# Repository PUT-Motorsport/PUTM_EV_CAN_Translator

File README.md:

# PUT Motorsport - CAN Translator
The module is responsible for communication between the motor inverter and the main bus. The translator transmits the speed set signals from the measurement card and logs the parameters from the inverter. All communication takes place over the CAN bus.

## Authors
* Piotr Kwiatkowski
* Bartosz Ptak

## Device
We used our own PCB, which was equipped with 2 CAN transmitters and a STM32F105RB microcontroller.

## Table of contents

- [Hardware setup](#Hardware-setup)
  * [Pinouts](#Pinouts)
  * [Clocks](#Clocks)
  * [Timers](#Timers)
  * [CANs](#CANs)
- [Software](#Software)
  * [CAN inverter functions](#CAN-inverter-functions)

## Hardware setup

### Pinouts

Active pinouts:

* CAN1_TX (`PA12`), CAN1_RX (`PA11`)
* CAN2_TX (`PB13`), CAN2_RX (`PB12`)
* RCC clock
* GPIO_LED_[1-6] for debugging

### Clocks

We used an external clock speed and set its frequency to **64 MHz** for (`HCLK`). This setting allowed to set the clock frequency of the peripherals to **32 MHz** (`PCLK1`).

### Timers

* `TIM2`:
    - **usage**: safety counting, 1 ms
    - **prescaler:** 999
    - **counter Period:** 63
    - **counter mode:** Up
    - **auto-reload:** Enable
* `TIM3`:
    - **usage**: send parameters to telemetry, 20 ms
    - **prescaler:** 19999
    - **counter Period:** 63
    - **counter mode:** Up
    - **auto-reload:** Enable

### CANs

* `CAN1`:
    - **usage**: main bus, measurement card, 500 kbps
    - **prescaler:** 4
    - **time quanta 1:** 13
    - **time quanta 2:** 2
    - **time quantum:** 125.0 ns

* `CAN2`:
    - **usage**: inverter bus, 500 kbps
    - **prescaler:** 4
    - **time quanta 1:** 13
    - **time quanta 2:** 2
    - **time quantum:** 125.0 ns

## Software

### CAN inverter functions

* `CAN_disable_controller_command` - inverter safety shutdown
* `CAN_set_speed_command` - set the APPS speed value in the range 0-500 (0-100%)
* `CAN_stop_speed_command` - set the speed value to 0
* `CAN_request_speed_command` - request that the inverter send information about the current speed
* `CAN_request_power_command` - request for the inverter to send information about the current current
* `CAN_request_igbt_temp_command` - request for the inverter to send information about the current igbt temperature
* `CAN_request_motor_temp_command` - request for the inverter to send information about the current motor temperature

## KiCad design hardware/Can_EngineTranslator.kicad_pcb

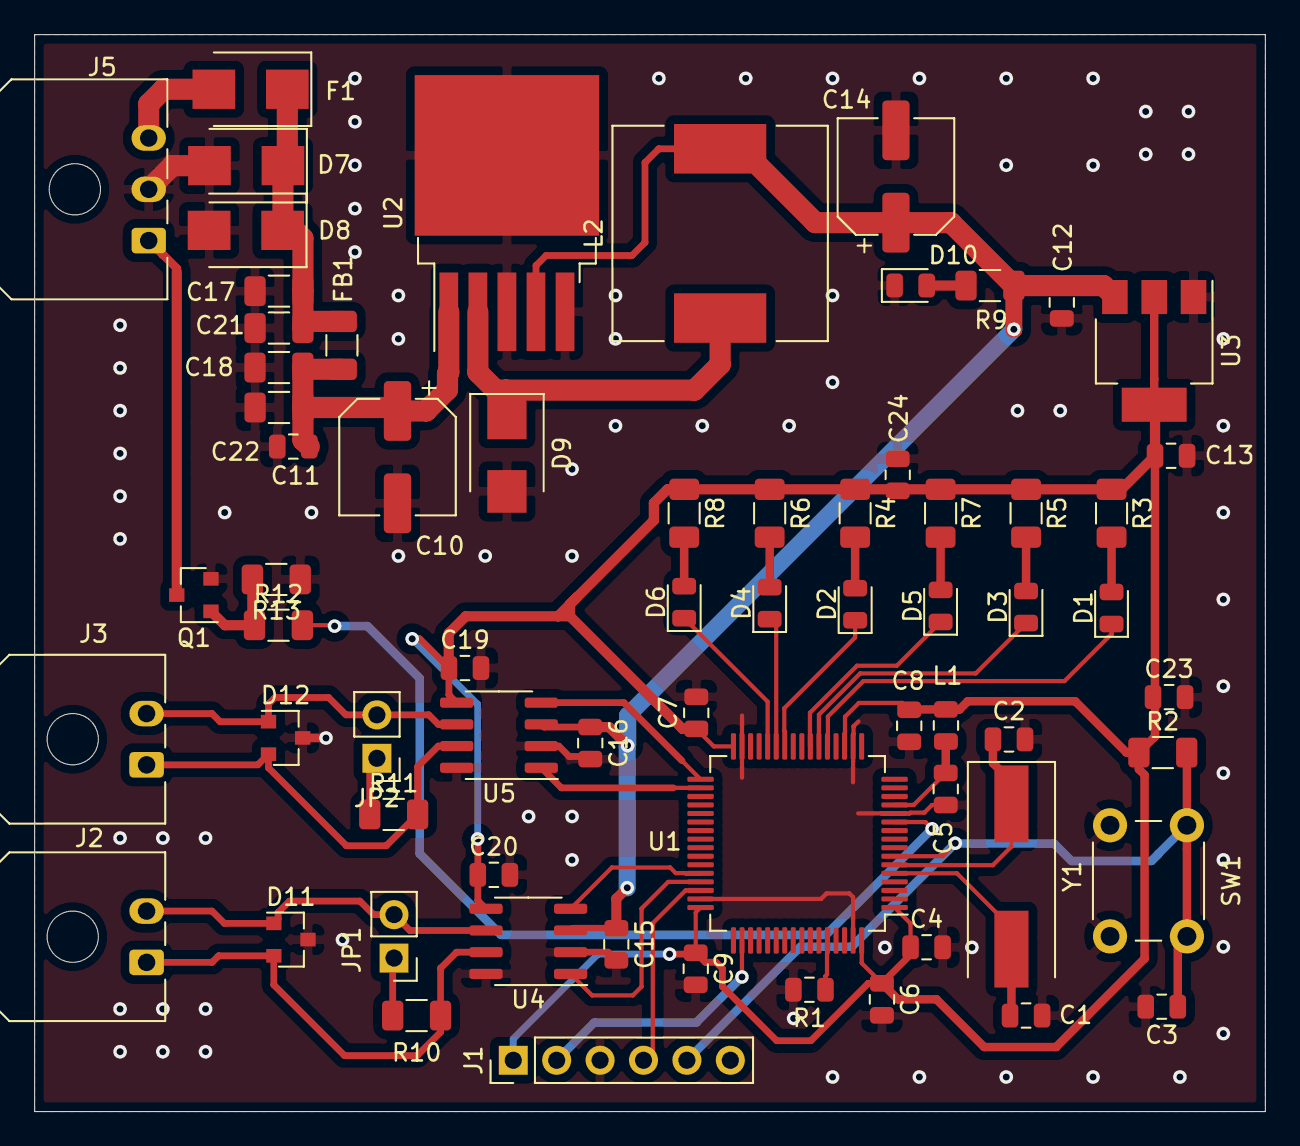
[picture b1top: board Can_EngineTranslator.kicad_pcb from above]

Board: 2 copper layers, 72.0 x 63.0 mm, 67 parts (0 on the bottom side), 40 nets.

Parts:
C1, C2: 22pF; C_0805_2012Metric
C3, C4, C5, C6, C7, C8, C9, C11, C12, C13, C15, C16, C19, C20, C23, C24: 100nF; C_0805_2012Metric
C10: 680uF; CP_Elec_6.3x7.7
C14: 220u; CP_Elec_6.3x7.7
C17, C18, C21, C22: CP_Small; C_1206_3216Metric
D1, D2, D3, D4, D5, D6, D10: LED; LED_0805_2012Metric
D7: 1SMA5937BT3G; D_SMB
D8, D9: SS24T3G; D_SMB
D11, D12: PESD2CAN.215; SOT-23
F1: Polyfuse; D_SMB
FB1: Ferrite_Bead_Small; R_1206_3216Metric
J1: ProgramerConnector; PinHeader_1x06_P2.54mm_Vertical
J2: CANcarConnector; Molex_Micro-Fit_3.0_43650-0200_1x02_P3.00mm_Horizontal
J3: CANinverterConnector; Molex_Micro-Fit_3.0_43650-0200_1x02_P3.00mm_Horizontal
J5: PowerOutputConnector; Molex_Micro-Fit_3.0_43650-0300_1x03_P3.00mm_Horizontal
JP1, JP2: Jumper; PinHeader_1x02_P2.54mm_Vertical
L1: L; L_0805_2012Metric
L2: 33u; L_12x12mm_H8mm
Q1: BSS138; SOT-23
R1: 100k; R_0805_2012Metric
R2, R13: 10k; R_1206_3216Metric
R3, R4, R5, R6, R7, R8, R9: 180; R_1206_3216Metric
R10, R11: 120R; R_1206_3216Metric
R12: 100; R_1206_3216Metric
SW1: SW_Push; SW_PUSH_6mm
U1: STM32F105RBTx; LQFP-64_10x10mm_P0.5mm
U2: LM2596S-5; TO-263-5_TabPin3
U3: LM1117-3.3; SOT-223-3_TabPin2
U4, U5: MCP2562-H-SN; SOIC-8_3.9x4.9mm_P1.27mm
Y1: Crystal 8 MHz; Crystal_SMD_HC49-SD

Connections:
+5V: C12.1, C14.1, C15.1, C16.1, L2.2, R9.1, U2.4, U3.3, U4.3, U5.3
CANcar_H: D11.2, J2.1, R10.2, U4.7
CANcar_L: D11.1, J2.2, JP1.2, U4.6
CANcar_RX: U1.44, U4.4
CANcar_TX: U1.45, U4.1
CANinverter_H: D12.2, J3.1, R11.2, U5.7
CANinverter_L: D12.1, J3.2, JP2.2, U5.6
CANinverter_RX: U1.33, U5.4
CANinverter_TX: U1.34, U5.1
NRST: C3.1, J1.5, R2.2, SW1.2, U1.7
unnamed: C1.1, U1.5, Y1.2
unnamed: C2.1, U1.6, Y1.1
unnamed: C5.1, L1.2, U1.13
unnamed: C10.1, C11.1, C18.1, C22.1, FB1.2, U2.1
unnamed: C17.1, C21.1, D7.1, D8.1, F1.1, FB1.1
unnamed: D1.1, U1.21
unnamed: D1.2, R3.2
unnamed: D2.1, U1.26
unnamed: D2.2, R4.2
unnamed: D3.1, U1.22
unnamed: D3.2, R5.2
unnamed: D4.1, U1.27
unnamed: D4.2, R6.2
unnamed: D5.1, U1.23
unnamed: D5.2, R7.2
unnamed: D6.1, U1.28
unnamed: D6.2, R8.2
unnamed: D9.1, L2.1, U2.2
unnamed: D10.2, R9.2
unnamed: JP1.1, R10.1
unnamed: JP2.1, R11.1
unnamed: Q1.1, R12.1, R13.2
unnamed: R1.1, U1.60
SWCLK: J1.2, U1.50
SWDIO: J1.4, U1.46
SW_GND: C1.2, C2.2, C3.2, C4.2, C5.2, C6.2, C7.2, C8.2, C9.2, C10.2, C11.2, C12.2, C13.2, C14.2, C15.2, C16.2, C17.2, C18.2, C19.2, C20.2, C21.2, C22.2, C23.2, C24.2, D7.2, D8.2, D9.2, D10.1, D11.3, D12.3, J1.3, J5.2, Q1.2, R1.2, R13.1, SW1.1, U1.12, U1.18, U1.31, U1.47, U1.63, U2.3, U2.5, U3.1, U4.2, U4.8, U5.2, U5.8
SW_VDDtarget: C4.1, C6.1, C7.1, C8.1, C9.1, C13.1, C19.1, C20.1, C23.1, C24.1, J1.1, L1.1, R2.1, R3.1, R4.1, R5.1, R6.1, R7.1, R8.1, U1.1, U1.19, U1.32, U1.48, U1.64, U3.2, U4.5, U5.5
VCC: F1.2, J5.3
buzzer: R12.2, U1.11
buzzer_gnd: J5.1, Q1.3

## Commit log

2020-09-27 Init project
2020-09-28 Add working baseline
2020-09-28 Add speed functions
2020-09-28 Update callbacks
2020-09-28 Update cobID
2020-09-28 Read speed value
2020-09-30 Update project
2020-10-02 some CAN is received and transmited
2020-10-02 Little cleanup
2020-10-02 added gitignore
2020-10-02 Add requests funcion and service
2020-10-02 Add apps communication and dissable engine
2020-10-03 Cleanup
2020-10-03 Add propably working timout system
2020-10-03 new project
2020-10-03 Update requests call time to 10ms
2020-10-03 Send fake apps signal 10ms regulary
2020-10-03 Ready for interrupts
2020-10-05 Added variables to store data from inverter TODO: get data from inverter, pack it to one frame, send it via CAN1.
2020-10-06 Something test, send data from inverter, repair hardware. Stick to your guns.
2020-10-06 All features. To test and adjust timers
2020-10-07 Add hardware description
2020-10-07 Add ToC
2020-10-12 Project works. Tested on car. No RPM, RMS and temp. TODO: data from inverted is wrong. Check it
2020-10-12 temp igbt works, to test
2020-10-25 RPM, engine temp and IGBT temp
2020-10-30 blocks controller when apps is too high
2020-10-31 Current working version.
2020-11-09 fixed latency problems
2020-11-12 Fixed delay
2020-11-19 another fix
2021-04-02 refactor
2021-04-02 moved stuff from inter. to main
2021-05-02 Files changed to actual version
2021-05-02 PCB Fixed
2021-05-02 Checked MJ
2021-05-10 Sync with Podio
2021-05-10 Connector change
2021-05-10 Cosmetic changes to pcb
2021-05-11 deleted mallocs and frees
2021-05-11 noticed magic numbers
2021-05-12 added TS_state, deleted engine_mode
2021-05-14 moved to main
2021-05-14 Move can init to function, deleted magic number
2021-05-16 fixed merging bug, added common.h for macros
2021-05-16 Transmit torque only when TS is ON
2021-05-18 grouped init functionality
2021-05-19 No torque transmission when APPS or inverter does not response
2021-05-19 Release update
2021-05-19 RTDS enabling sound
2021-06-04 RTDS enable vars
2021-06-22 some cleaning
2021-06-22 reapired pcb
2021-07-06 Added ts on/off functionality, change CAN ID, RTDS duration, CAN filters
2021-07-06 forgot to uncomment stuff
2021-07-06 Sugested tweaks
2021-08-01 deleted CAN filters
